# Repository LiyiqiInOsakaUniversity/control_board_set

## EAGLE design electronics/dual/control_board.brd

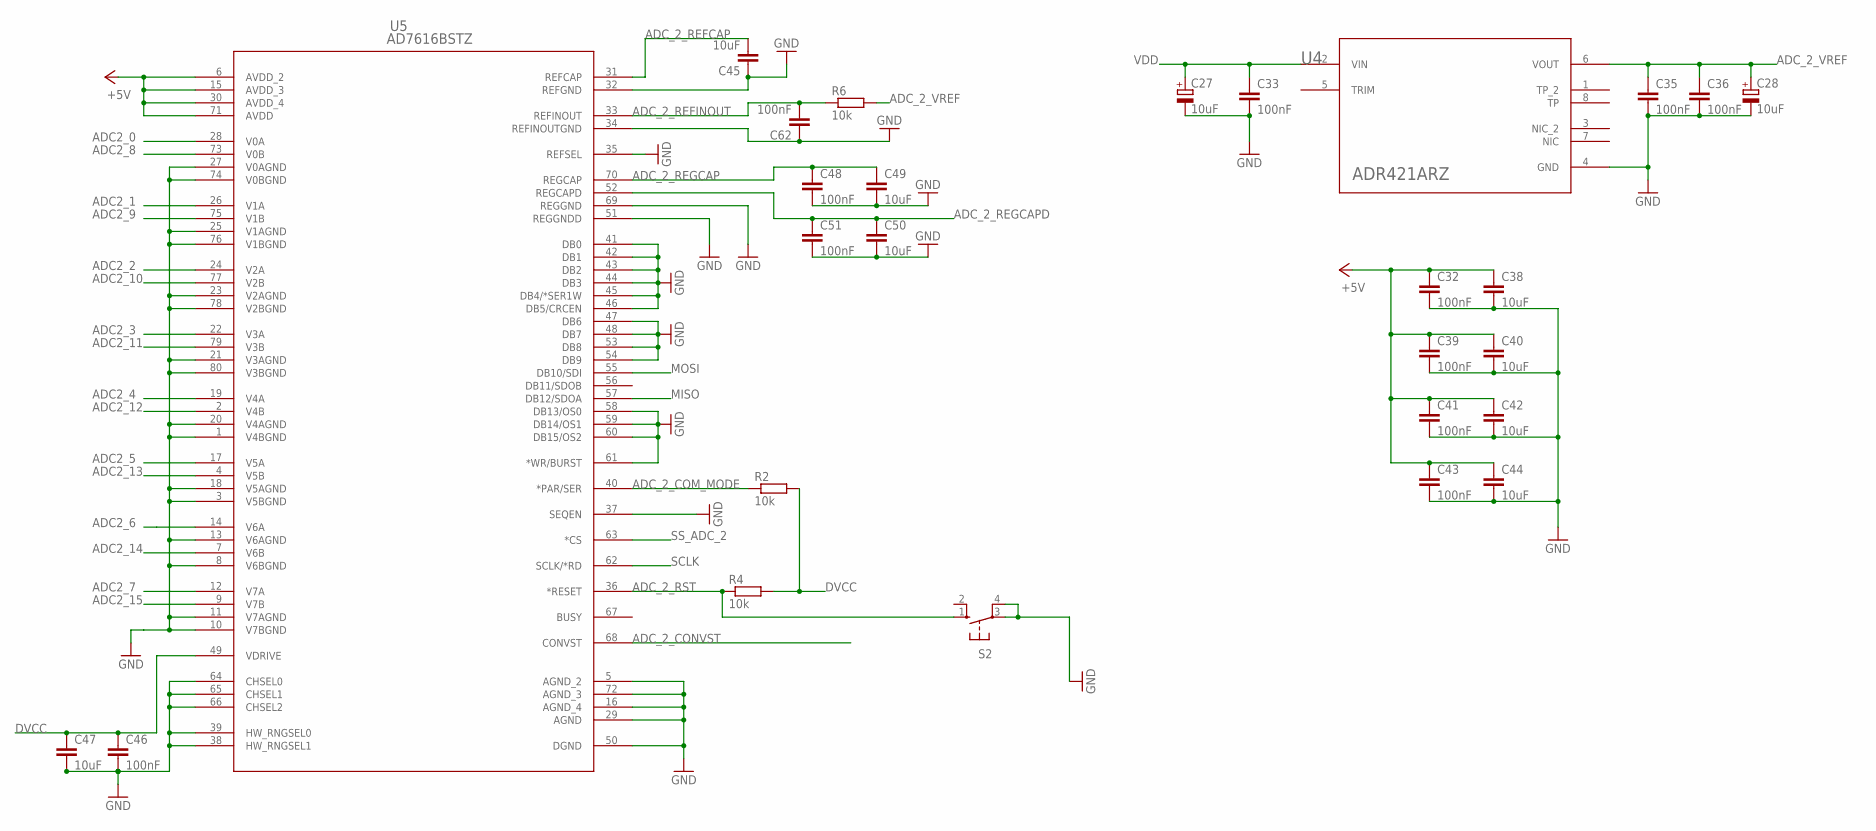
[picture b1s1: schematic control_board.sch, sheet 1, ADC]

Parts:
C27, C28: 10uF; SMC_A
C32, C33, C35, C36, C39, C41, C43, C46, C48, C51, C62: 100nF; C0603
C38, C40, C42, C44, C45, C47, C49, C50: 10uF; C0603
R2, R4, R6: 10k; R0603
S2: 10-XX; B3F-10XX
U4: ADR421ARZ; R_8
U5: AD7616BSTZ; ST_80_2

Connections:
+5V: C32.1, C38.1, C39.1, C40.1, C41.1, C42.1, C43.1, C44.1, U5.6 (AVDD_2), U5.15 (AVDD_3), U5.30 (AVDD_4), U5.71 (AVDD); also elsewhere on the board
ADC2_0: U5.28 (V0A); also elsewhere on the board
ADC2_1: U5.26 (V1A); also elsewhere on the board
ADC2_2: U5.24 (V2A); also elsewhere on the board
ADC2_3: U5.22 (V3A); also elsewhere on the board
ADC2_4: U5.19 (V4A); also elsewhere on the board
ADC2_5: U5.17 (V5A); also elsewhere on the board
ADC2_6: U5.14 (V6A); also elsewhere on the board
ADC2_7: U5.12 (V7A); also elsewhere on the board
ADC2_8: U5.73 (V0B); also elsewhere on the board
ADC2_9: U5.75 (V1B); also elsewhere on the board
ADC2_10: U5.77 (V2B); also elsewhere on the board
ADC2_11: U5.79 (V3B); also elsewhere on the board
ADC2_12: U5.2 (V4B); also elsewhere on the board
ADC2_13: U5.4 (V5B); also elsewhere on the board
ADC2_14: U5.7 (V6B); also elsewhere on the board
ADC2_15: U5.9 (V7B); also elsewhere on the board
ADC_2_COM_MODE: R2.1, U5.40 (*PAR/SER)
ADC_2_CONVST: U5.68 (CONVST); also elsewhere on the board
ADC_2_REFCAP: C45.2, U5.31 (REFCAP)
ADC_2_REFINOUT: C62.2, R6.1, U5.33 (REFINOUT)
ADC_2_REGCAP: C48.1, C49.1, U5.70 (REGCAP)
ADC_2_REGCAPD: C50.1, C51.1, U5.52 (REGCAPD)
ADC_2_RST: R4.1, S2.1 (S), U5.36 (*RESET)
ADC_2_VREF: C28.+, C35.1, C36.1, R6.2, U4.6 (VOUT)
DVCC: C46.1, C47.1, R2.2, R4.2, U5.49 (VDRIVE); also elsewhere on the board
GND: C27.-, C28.-, C32.2, C33.2, C35.2, C36.2, C38.2, C39.2, C40.2, C41.2, C42.2, C43.2, C44.2, C45.1, C46.2, C47.2, C48.2, C49.2, C50.2, C51.2, C62.1, S2.3, S2.4 (P1), U4.4 (GND), U5.1 (V4BGND), U5.3 (V5BGND), U5.5 (AGND_2), U5.8 (V6BGND), U5.10 (V7BGND), U5.11 (V7AGND), U5.13 (V6AGND), U5.16 (AGND_4), U5.18 (V5AGND), U5.20 (V4AGND), U5.21 (V3AGND), U5.23 (V2AGND), U5.25 (V1AGND), U5.27 (V0AGND), U5.29 (AGND), U5.32 (REFGND), U5.34 (REFINOUTGND), U5.35 (REFSEL), U5.37 (SEQEN), U5.38 (HW_RNGSEL1), U5.39 (HW_RNGSEL0), U5.41 (DB0), U5.42 (DB1), U5.43 (DB2), U5.44 (DB3), U5.45 (DB4/*SER1W), U5.46 (DB5/CRCEN), U5.47 (DB6), U5.48 (DB7), U5.50 (DGND), U5.51 (REGGNDD), U5.53 (DB8), U5.54 (DB9), U5.58 (DB13/OS0), U5.59 (DB14/OS1), U5.60 (DB15/OS2), U5.61 (*WR/BURST), U5.64 (CHSEL0), U5.65 (CHSEL1), U5.66 (CHSEL2), U5.69 (REGGND), U5.72 (AGND_3), U5.74 (V0BGND), U5.76 (V1BGND), U5.78 (V2BGND), U5.80 (V3BGND); also elsewhere on the board
MISO: U5.57 (DB12/SDOA); also elsewhere on the board
MOSI: U5.55 (DB10/SDI); also elsewhere on the board
SCLK: U5.62 (SCLK/*RD); also elsewhere on the board
SS_ADC_2: U5.63 (*CS); also elsewhere on the board
VDD: C27.+, C33.1, U4.2 (VIN); also elsewhere on the board

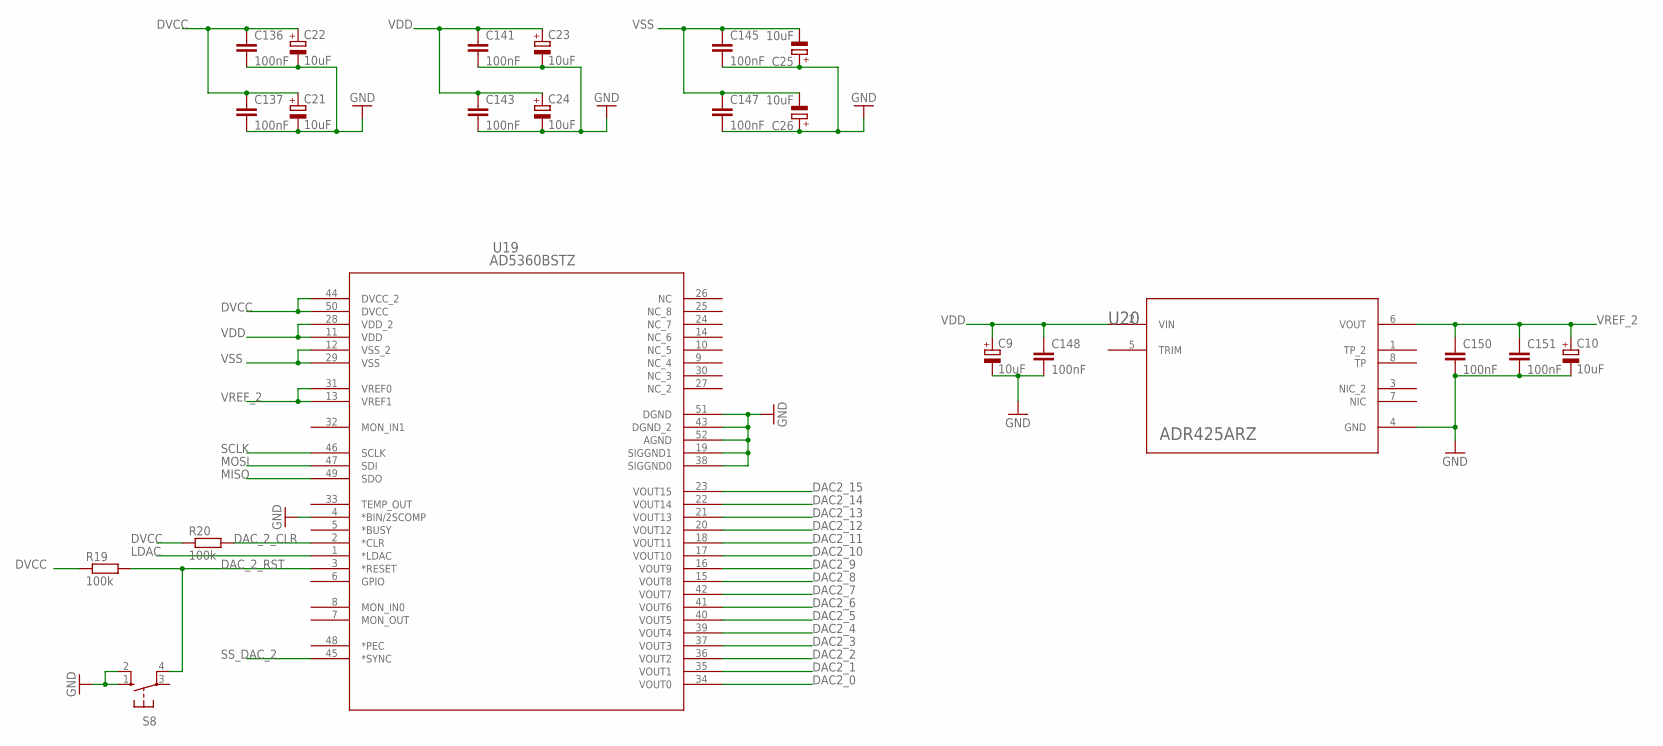
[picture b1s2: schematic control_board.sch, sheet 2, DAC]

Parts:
C9, C10, C21, C22, C23, C24, C25, C26: 10uF; SMC_A
C136, C137, C141, C143, C145, C147, C148, C150, C151: 100nF; C0603
R19, R20: 100k; R0603
S8: 10-XX; B3F-10XX
U19: AD5360BSTZ; ST_52
U20: ADR425ARZ; R_8

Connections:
DAC2_0: U19.34 (VOUT0); also elsewhere on the board
DAC2_1: U19.35 (VOUT1); also elsewhere on the board
DAC2_2: U19.36 (VOUT2); also elsewhere on the board
DAC2_3: U19.37 (VOUT3); also elsewhere on the board
DAC2_4: U19.39 (VOUT4); also elsewhere on the board
DAC2_5: U19.40 (VOUT5); also elsewhere on the board
DAC2_6: U19.41 (VOUT6); also elsewhere on the board
DAC2_7: U19.42 (VOUT7); also elsewhere on the board
DAC2_8: U19.15 (VOUT8); also elsewhere on the board
DAC2_9: U19.16 (VOUT9); also elsewhere on the board
DAC2_10: U19.17 (VOUT10); also elsewhere on the board
DAC2_11: U19.18 (VOUT11); also elsewhere on the board
DAC2_12: U19.20 (VOUT12); also elsewhere on the board
DAC2_13: U19.21 (VOUT13); also elsewhere on the board
DAC2_14: U19.22 (VOUT14); also elsewhere on the board
DAC2_15: U19.23 (VOUT15); also elsewhere on the board
DAC_2_CLR: R20.2, U19.2 (*CLR)
DAC_2_RST: R19.2, S8.4 (P1), U19.3 (*RESET)
DVCC: C21.+, C22.+, C136.1, C137.1, R19.1, R20.1, U19.44 (DVCC_2), U19.50 (DVCC); also elsewhere on the board
GND: C9.-, C10.-, C21.-, C22.-, C23.-, C24.-, C25.+, C26.+, C136.2, C137.2, C141.2, C143.2, C145.2, C147.2, C148.2, C150.2, C151.2, S8.1 (S), S8.2 (S1), U19.4 (*BIN/2SCOMP), U19.19 (SIGGND1), U19.38 (SIGGND0), U19.43 (DGND_2), U19.51 (DGND), U19.52 (AGND), U20.4 (GND); also elsewhere on the board
LDAC: U19.1 (*LDAC); also elsewhere on the board
MISO: U19.49 (SDO); also elsewhere on the board
MOSI: U19.47 (SDI); also elsewhere on the board
SCLK: U19.46 (SCLK); also elsewhere on the board
SS_DAC_2: U19.45 (*SYNC); also elsewhere on the board
VDD: C9.+, C23.+, C24.+, C141.1, C143.1, C148.1, U19.11 (VDD), U19.28 (VDD_2), U20.2 (VIN); also elsewhere on the board
VREF_2: C10.+, C150.1, C151.1, U19.13 (VREF1), U19.31 (VREF0), U20.6 (VOUT)
VSS: C25.-, C26.-, C145.1, C147.1, U19.12 (VSS_2), U19.29 (VSS); also elsewhere on the board

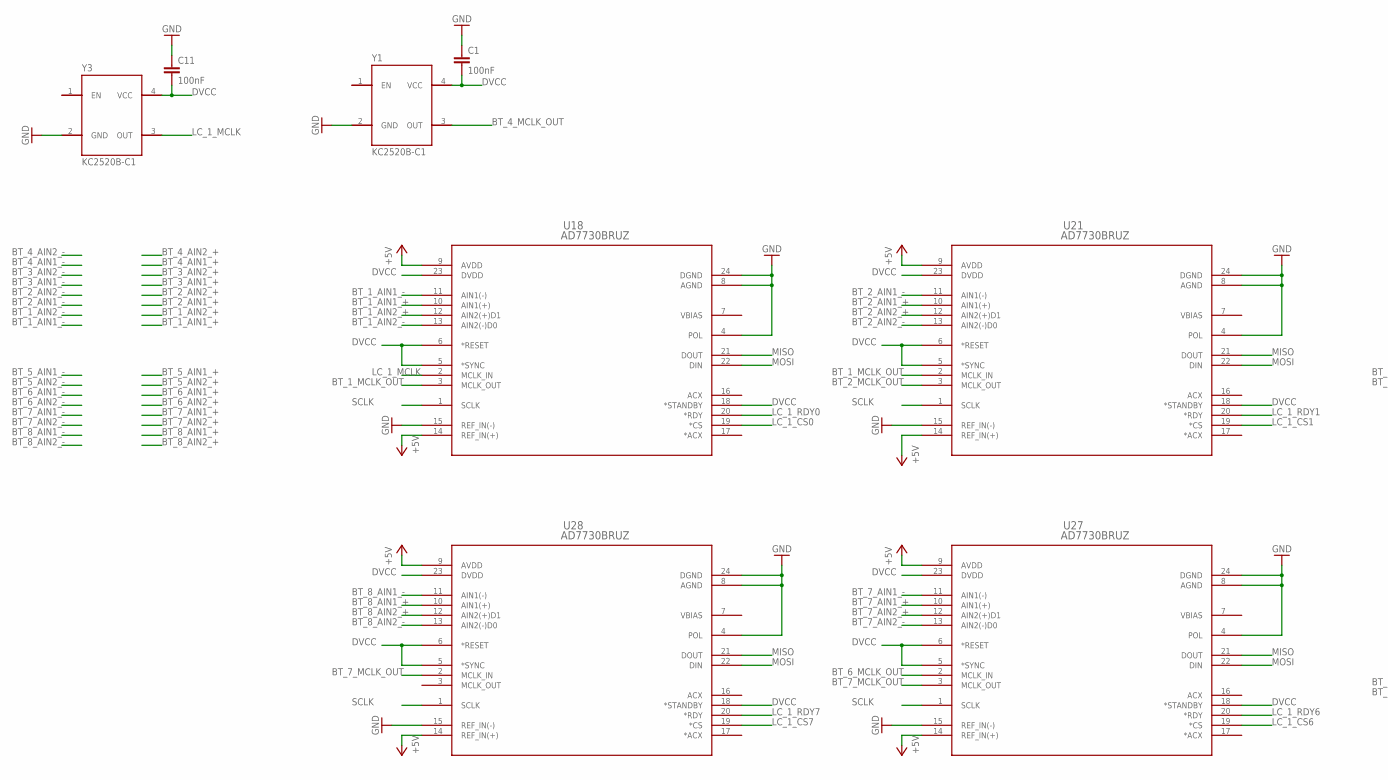
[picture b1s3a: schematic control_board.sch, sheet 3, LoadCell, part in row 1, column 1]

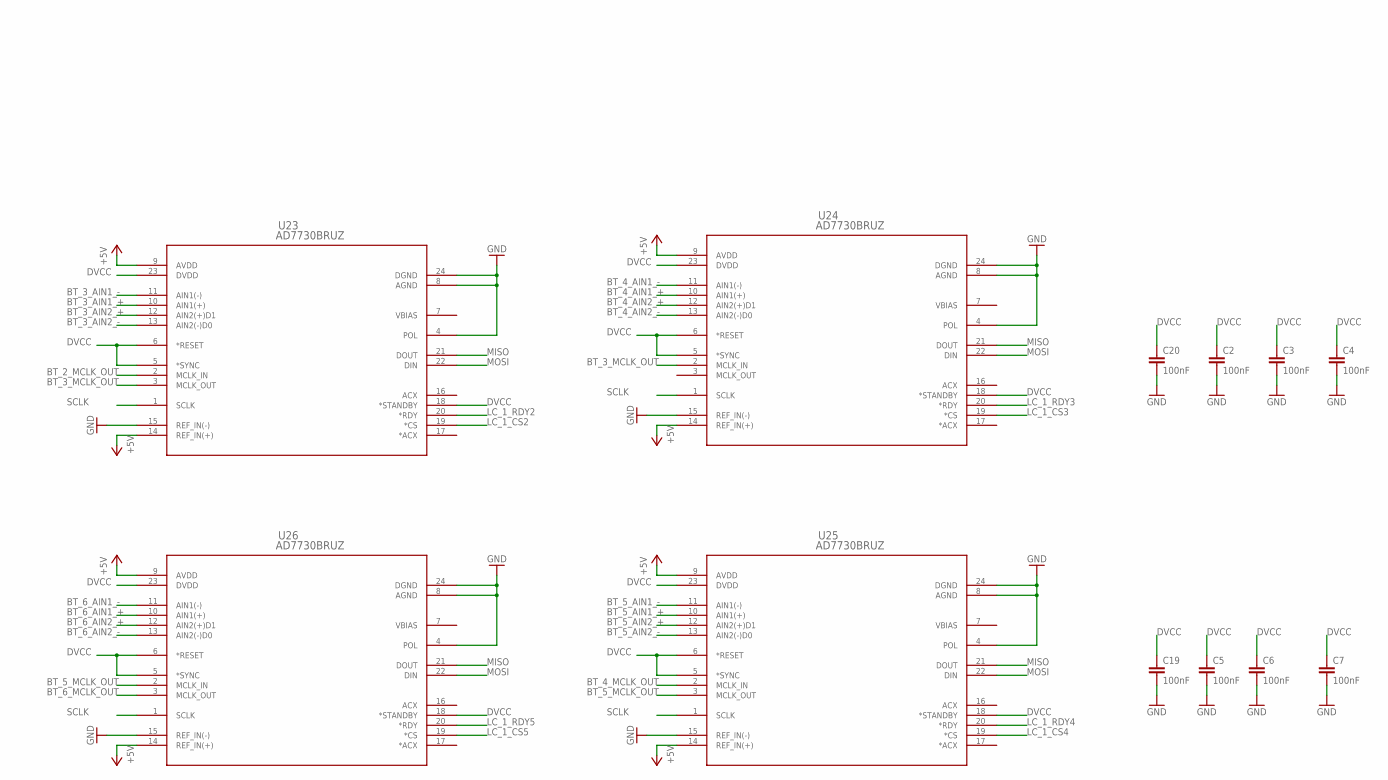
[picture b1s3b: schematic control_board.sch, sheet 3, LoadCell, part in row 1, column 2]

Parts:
C1, C2, C3, C4, C5, C6, C7, C11, C19, C20: 100nF; C0603
U18, U21, U23, U24, U25, U26, U27, U28: AD7730BRUZ; RU_24
Y1, Y3: KC2520B-C1

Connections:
+5V: U18.9 (AVDD), U18.14 (REF_IN(+)), U21.9 (AVDD), U21.14 (REF_IN(+)), U23.9 (AVDD), U23.14 (REF_IN(+)), U24.9 (AVDD), U24.14 (REF_IN(+)), U25.9 (AVDD), U25.14 (REF_IN(+)), U26.9 (AVDD), U26.14 (REF_IN(+)), U27.9 (AVDD), U27.14 (REF_IN(+)), U28.9 (AVDD), U28.14 (REF_IN(+)); also elsewhere on the board
BT_1_AIN1_+: U18.10 (AIN1(+)); also elsewhere on the board
BT_1_AIN1_-: U18.11 (AIN1(-)); also elsewhere on the board
BT_1_AIN2_+: U18.12 (AIN2(+)D1); also elsewhere on the board
BT_1_AIN2_-: U18.13 (AIN2(-)D0); also elsewhere on the board
BT_1_MCLK_OUT: U18.3 (MCLK_OUT), U21.2 (MCLK_IN)
BT_2_AIN1_+: U21.10 (AIN1(+)); also elsewhere on the board
BT_2_AIN1_-: U21.11 (AIN1(-)); also elsewhere on the board
BT_2_AIN2_+: U21.12 (AIN2(+)D1); also elsewhere on the board
BT_2_AIN2_-: U21.13 (AIN2(-)D0); also elsewhere on the board
BT_2_MCLK_OUT: U21.3 (MCLK_OUT), U23.2 (MCLK_IN)
BT_3_AIN1_+: U23.10 (AIN1(+)); also elsewhere on the board
BT_3_AIN1_-: U23.11 (AIN1(-)); also elsewhere on the board
BT_3_AIN2_+: U23.12 (AIN2(+)D1); also elsewhere on the board
BT_3_AIN2_-: U23.13 (AIN2(-)D0); also elsewhere on the board
BT_3_MCLK_OUT: U23.3 (MCLK_OUT), U24.2 (MCLK_IN)
BT_4_AIN1_+: U24.10 (AIN1(+)); also elsewhere on the board
BT_4_AIN1_-: U24.11 (AIN1(-)); also elsewhere on the board
BT_4_AIN2_+: U24.12 (AIN2(+)D1); also elsewhere on the board
BT_4_AIN2_-: U24.13 (AIN2(-)D0); also elsewhere on the board
BT_4_MCLK_OUT: U25.2 (MCLK_IN), Y1.3 (OUT)
BT_5_AIN1_+: U25.10 (AIN1(+)); also elsewhere on the board
BT_5_AIN1_-: U25.11 (AIN1(-)); also elsewhere on the board
BT_5_AIN2_+: U25.12 (AIN2(+)D1); also elsewhere on the board
BT_5_AIN2_-: U25.13 (AIN2(-)D0); also elsewhere on the board
BT_5_MCLK_OUT: U25.3 (MCLK_OUT), U26.2 (MCLK_IN)
BT_6_AIN1_+: U26.10 (AIN1(+)); also elsewhere on the board
BT_6_AIN1_-: U26.11 (AIN1(-)); also elsewhere on the board
BT_6_AIN2_+: U26.12 (AIN2(+)D1); also elsewhere on the board
BT_6_AIN2_-: U26.13 (AIN2(-)D0); also elsewhere on the board
BT_6_MCLK_OUT: U26.3 (MCLK_OUT), U27.2 (MCLK_IN)
BT_7_AIN1_+: U27.10 (AIN1(+)); also elsewhere on the board
BT_7_AIN1_-: U27.11 (AIN1(-)); also elsewhere on the board
BT_7_AIN2_+: U27.12 (AIN2(+)D1); also elsewhere on the board
BT_7_AIN2_-: U27.13 (AIN2(-)D0); also elsewhere on the board
BT_7_MCLK_OUT: U27.3 (MCLK_OUT), U28.2 (MCLK_IN)
BT_8_AIN1_+: U28.10 (AIN1(+)); also elsewhere on the board
BT_8_AIN1_-: U28.11 (AIN1(-)); also elsewhere on the board
BT_8_AIN2_+: U28.12 (AIN2(+)D1); also elsewhere on the board
BT_8_AIN2_-: U28.13 (AIN2(-)D0); also elsewhere on the board
DVCC: C1.2, C2.1, C3.1, C4.1, C5.1, C6.1, C7.1, C11.2, C19.1, C20.1, U18.5 (*SYNC), U18.6 (*RESET), U18.18 (*STANDBY), U18.23 (DVDD), U21.5 (*SYNC), U21.6 (*RESET), U21.18 (*STANDBY), U21.23 (DVDD), U23.5 (*SYNC), U23.6 (*RESET), U23.18 (*STANDBY), U23.23 (DVDD), U24.5 (*SYNC), U24.6 (*RESET), U24.18 (*STANDBY), U24.23 (DVDD), U25.5 (*SYNC), U25.6 (*RESET), U25.18 (*STANDBY), U25.23 (DVDD), U26.5 (*SYNC), U26.6 (*RESET), U26.18 (*STANDBY), U26.23 (DVDD), U27.5 (*SYNC), U27.6 (*RESET), U27.18 (*STANDBY), U27.23 (DVDD), U28.5 (*SYNC), U28.6 (*RESET), U28.18 (*STANDBY), U28.23 (DVDD), Y1.4 (VCC), Y3.4 (VCC); also elsewhere on the board
GND: C1.1, C2.2, C3.2, C4.2, C5.2, C6.2, C7.2, C11.1, C19.2, C20.2, U18.4 (POL), U18.8 (AGND), U18.15 (REF_IN(-)), U18.24 (DGND), U21.4 (POL), U21.8 (AGND), U21.15 (REF_IN(-)), U21.24 (DGND), U23.4 (POL), U23.8 (AGND), U23.15 (REF_IN(-)), U23.24 (DGND), U24.4 (POL), U24.8 (AGND), U24.15 (REF_IN(-)), U24.24 (DGND), U25.4 (POL), U25.8 (AGND), U25.15 (REF_IN(-)), U25.24 (DGND), U26.4 (POL), U26.8 (AGND), U26.15 (REF_IN(-)), U26.24 (DGND), U27.4 (POL), U27.8 (AGND), U27.15 (REF_IN(-)), U27.24 (DGND), U28.4 (POL), U28.8 (AGND), U28.15 (REF_IN(-)), U28.24 (DGND), Y1.2 (GND), Y3.2 (GND); also elsewhere on the board
LC_1_CS0: U18.19 (*CS); also elsewhere on the board
LC_1_CS1: U21.19 (*CS); also elsewhere on the board
LC_1_CS2: U23.19 (*CS); also elsewhere on the board
LC_1_CS3: U24.19 (*CS); also elsewhere on the board
LC_1_CS4: U25.19 (*CS); also elsewhere on the board
LC_1_CS5: U26.19 (*CS); also elsewhere on the board
LC_1_CS6: U27.19 (*CS); also elsewhere on the board
LC_1_CS7: U28.19 (*CS); also elsewhere on the board
LC_1_MCLK: U18.2 (MCLK_IN), Y3.3 (OUT)
LC_1_RDY0: U18.20 (*RDY); also elsewhere on the board
LC_1_RDY1: U21.20 (*RDY); also elsewhere on the board
LC_1_RDY2: U23.20 (*RDY); also elsewhere on the board
LC_1_RDY3: U24.20 (*RDY); also elsewhere on the board
LC_1_RDY4: U25.20 (*RDY); also elsewhere on the board
LC_1_RDY5: U26.20 (*RDY); also elsewhere on the board
LC_1_RDY6: U27.20 (*RDY); also elsewhere on the board
LC_1_RDY7: U28.20 (*RDY); also elsewhere on the board
MISO: U18.21 (DOUT), U21.21 (DOUT), U23.21 (DOUT), U24.21 (DOUT), U25.21 (DOUT), U26.21 (DOUT), U27.21 (DOUT), U28.21 (DOUT); also elsewhere on the board
MOSI: U18.22 (DIN), U21.22 (DIN), U23.22 (DIN), U24.22 (DIN), U25.22 (DIN), U26.22 (DIN), U27.22 (DIN), U28.22 (DIN); also elsewhere on the board
SCLK: U18.1 (SCLK), U21.1 (SCLK), U23.1 (SCLK), U24.1 (SCLK), U25.1 (SCLK), U26.1 (SCLK), U27.1 (SCLK), U28.1 (SCLK); also elsewhere on the board

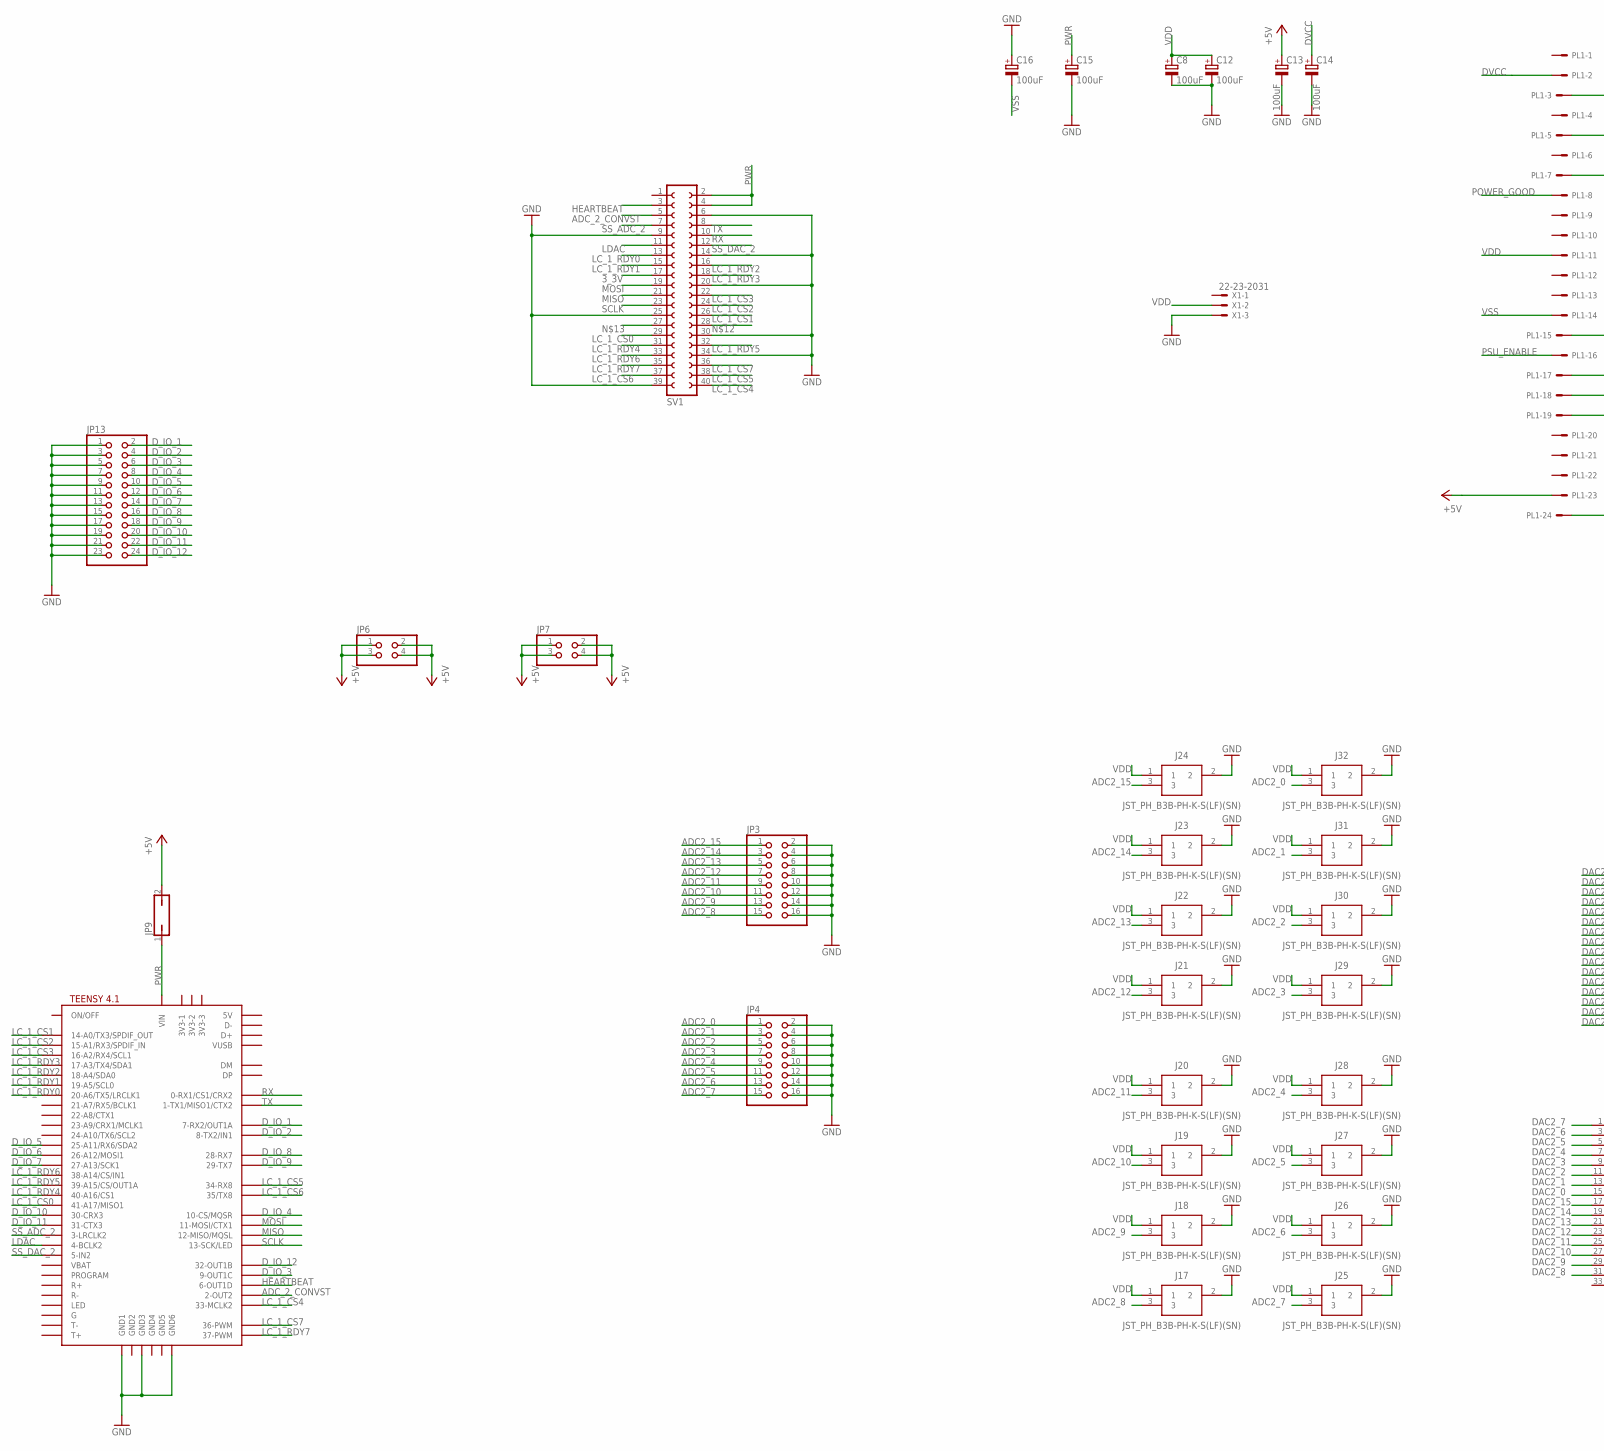
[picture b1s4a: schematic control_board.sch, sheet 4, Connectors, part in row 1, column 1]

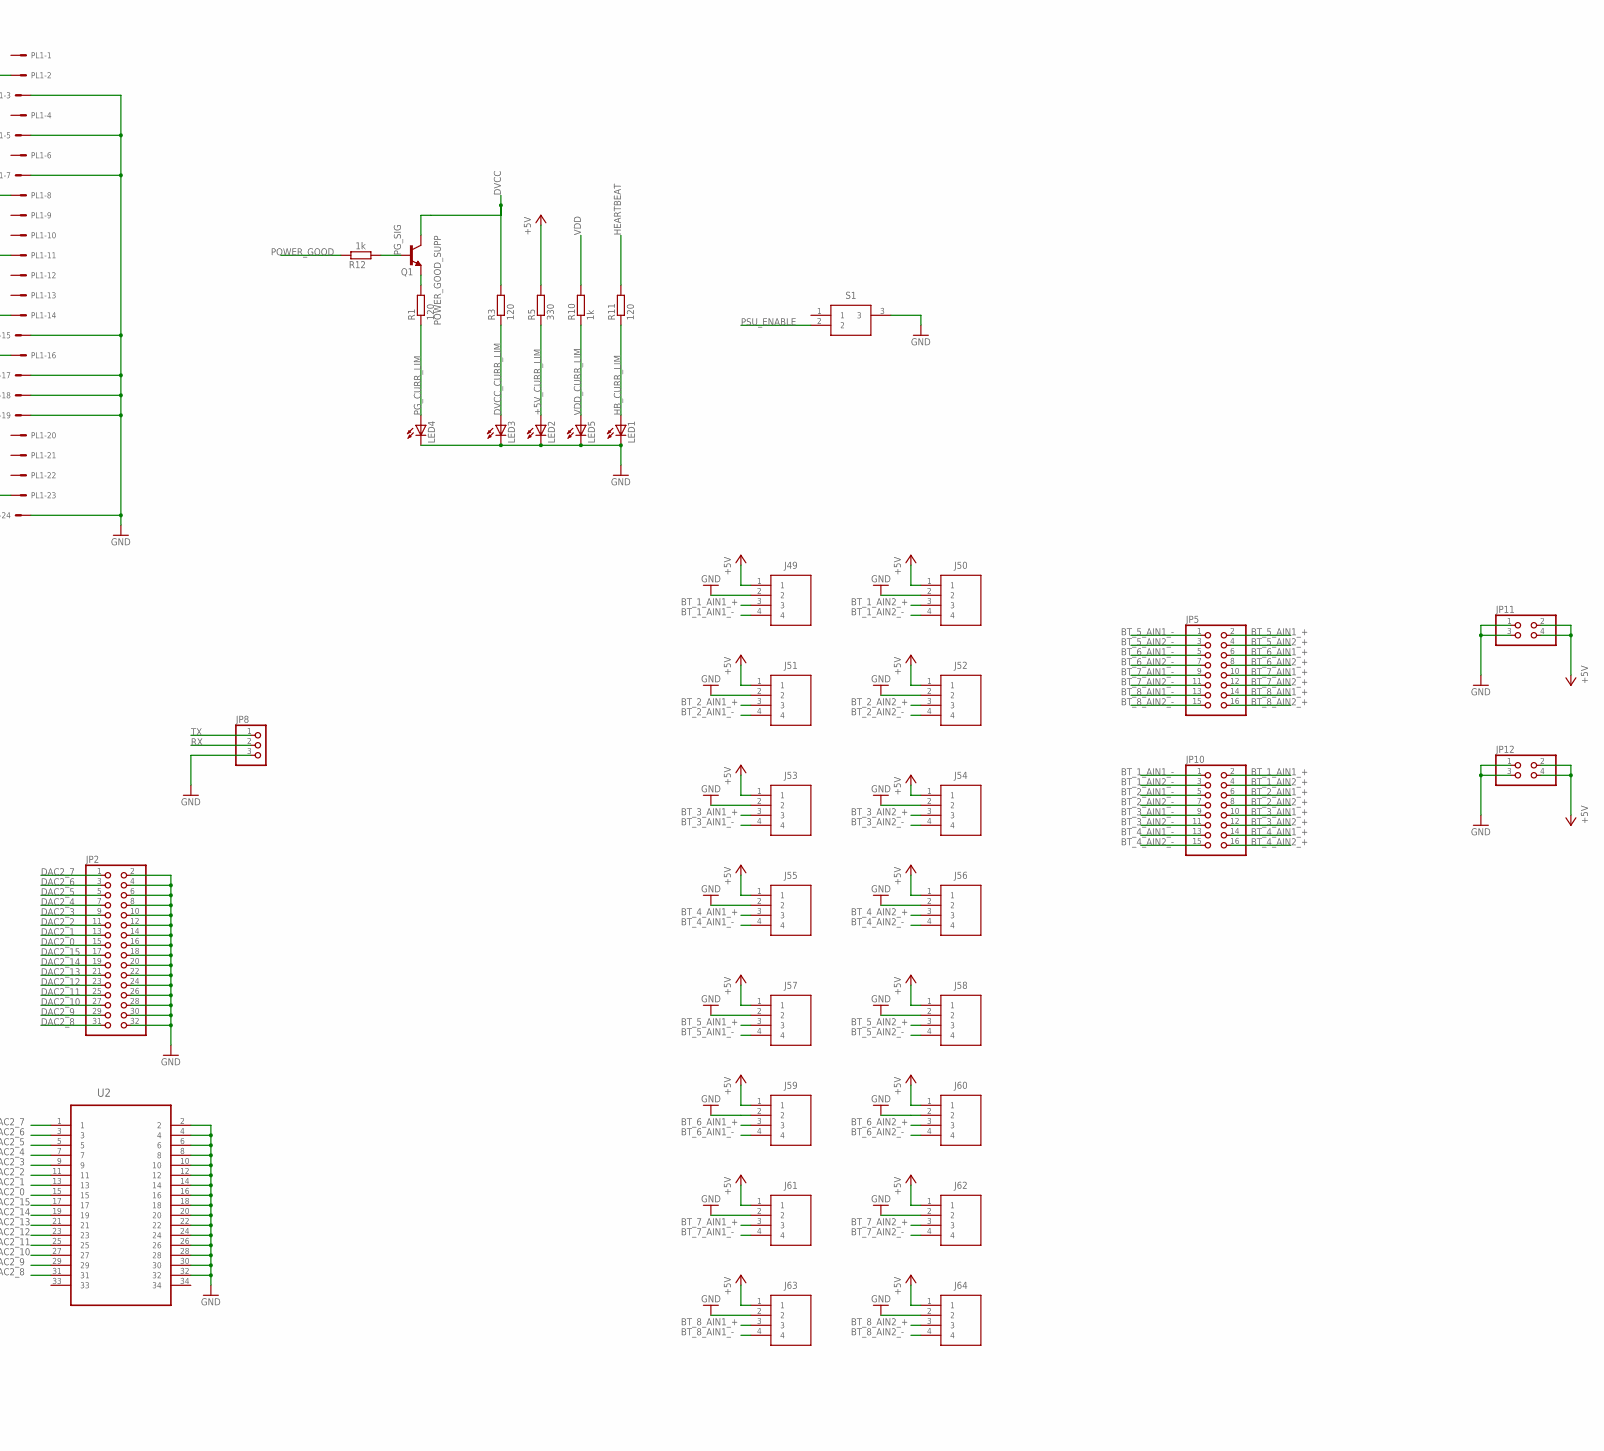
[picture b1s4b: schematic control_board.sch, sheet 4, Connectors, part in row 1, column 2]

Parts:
C8, C12, C13, C14, C15, C16: 100uF; E3,5-8
J17, J18, J19, J20, J21, J22, J23, J24, J25, J26, J27, J28, J29, J30, J31, J32: JST_PH_B3B-PH-K-S(LF)(SN); JST_PH_SHDR3W50P0X200_1X3_790X450X600
J49, J50, J51, J52, J53, J54, J55, J56, J57, J58, J59, J60, J61, J62, J63, J64: B4B-PH-K-S(LF)(SN); SHDR4W50P0X200_1X4_990X450X600
JP2: PINHD-2X16/90; 2X16/90
JP3, JP4: PINHD-2X8/90; 2X08/90
JP5, JP10: PINHD-2X8; 2X08
JP6, JP7: PINHD-2X2/90; 2X02/90
JP8: PINHD-1X3; 1X03
JP9: JP1Q; JP1
JP11, JP12: PINHD-2X2; 2X02
JP13: PINHD-2X12_2.54-SMD; 2X12SMD
LED1, LED2, LED3, LED4, LED5: LEDCHIP-LED0603; CHIP-LED0603
PL1: 555X-24V; 5566-24
Q1: BCF29SMD; SOT23-BEC
R1, R3, R11: 120; R0805
R5: 330; R0805
R10, R12: 1k; R0805
S1: 1MS1T1B1M2QES-5
SV1: FE20-2
U2: AMP-5103309-7-34PIN_5103309-7; AMP-5103309-7-34PIN_TYCO_5103309-7
U$1: TEENSY41
X1: 22-23-2031

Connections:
3_3V: SV1.17
+5V: C13.+, J49.1, J50.1, J51.1, J52.1, J53.1, J54.1, J55.1, J56.1, J57.1, J58.1, J59.1, J60.1, J61.1, J62.1, J63.1, J64.1, JP6.1, JP6.2, JP6.3, JP6.4, JP7.1, JP7.2, JP7.3, JP7.4, JP9.2, JP11.2, JP11.4, JP12.2, JP12.4, PL1.23, R5.2; also elsewhere on the board
+5V_CURR_LIM: LED2.A, R5.1
ADC2_0: J32.3, JP4.1; also elsewhere on the board
ADC2_1: J31.3, JP4.3; also elsewhere on the board
ADC2_2: J30.3, JP4.5; also elsewhere on the board
ADC2_3: J29.3, JP4.7; also elsewhere on the board
ADC2_4: J28.3, JP4.9; also elsewhere on the board
ADC2_5: J27.3, JP4.11; also elsewhere on the board
ADC2_6: J26.3, JP4.13; also elsewhere on the board
ADC2_7: J25.3, JP4.15; also elsewhere on the board
ADC2_8: J17.3, JP3.15; also elsewhere on the board
ADC2_9: J18.3, JP3.13; also elsewhere on the board
ADC2_10: J19.3, JP3.11; also elsewhere on the board
ADC2_11: J20.3, JP3.9; also elsewhere on the board
ADC2_12: J21.3, JP3.7; also elsewhere on the board
ADC2_13: J22.3, JP3.5; also elsewhere on the board
ADC2_14: J23.3, JP3.3; also elsewhere on the board
ADC2_15: J24.3, JP3.1; also elsewhere on the board
ADC_2_CONVST: SV1.5, U$1.2-OUT2; also elsewhere on the board
BT_1_AIN1_+: J49.3, JP10.2; also elsewhere on the board
BT_1_AIN1_-: J49.4, JP10.1; also elsewhere on the board
BT_1_AIN2_+: J50.3, JP10.4; also elsewhere on the board
BT_1_AIN2_-: J50.4, JP10.3; also elsewhere on the board
BT_2_AIN1_+: J51.3, JP10.6; also elsewhere on the board
BT_2_AIN1_-: J51.4, JP10.5; also elsewhere on the board
BT_2_AIN2_+: J52.3, JP10.8; also elsewhere on the board
BT_2_AIN2_-: J52.4, JP10.7; also elsewhere on the board
BT_3_AIN1_+: J53.3, JP10.10; also elsewhere on the board
BT_3_AIN1_-: J53.4, JP10.9; also elsewhere on the board
BT_3_AIN2_+: J54.3, JP10.12; also elsewhere on the board
BT_3_AIN2_-: J54.4, JP10.11; also elsewhere on the board
BT_4_AIN1_+: J55.3, JP10.14; also elsewhere on the board
BT_4_AIN1_-: J55.4, JP10.13; also elsewhere on the board
BT_4_AIN2_+: J56.3, JP10.16; also elsewhere on the board
BT_4_AIN2_-: J56.4, JP10.15; also elsewhere on the board
BT_5_AIN1_+: J57.3, JP5.2; also elsewhere on the board
BT_5_AIN1_-: J57.4, JP5.1; also elsewhere on the board
BT_5_AIN2_+: J58.3, JP5.4; also elsewhere on the board
BT_5_AIN2_-: J58.4, JP5.3; also elsewhere on the board
BT_6_AIN1_+: J59.3, JP5.6; also elsewhere on the board
BT_6_AIN1_-: J59.4, JP5.5; also elsewhere on the board
BT_6_AIN2_+: J60.3, JP5.8; also elsewhere on the board
BT_6_AIN2_-: J60.4, JP5.7; also elsewhere on the board
BT_7_AIN1_+: J61.3, JP5.10; also elsewhere on the board
BT_7_AIN1_-: J61.4, JP5.9; also elsewhere on the board
BT_7_AIN2_+: J62.3, JP5.12; also elsewhere on the board
BT_7_AIN2_-: J62.4, JP5.11; also elsewhere on the board
BT_8_AIN1_+: J63.3, JP5.14; also elsewhere on the board
BT_8_AIN1_-: J63.4, JP5.13; also elsewhere on the board
BT_8_AIN2_+: J64.3, JP5.16; also elsewhere on the board
BT_8_AIN2_-: J64.4, JP5.15; also elsewhere on the board
DAC2_0: JP2.15, U2.15; also elsewhere on the board
DAC2_1: JP2.13, U2.13; also elsewhere on the board
DAC2_2: JP2.11, U2.11; also elsewhere on the board
DAC2_3: JP2.9, U2.9; also elsewhere on the board
DAC2_4: JP2.7, U2.7; also elsewhere on the board
DAC2_5: JP2.5, U2.5; also elsewhere on the board
DAC2_6: JP2.3, U2.3; also elsewhere on the board
DAC2_7: JP2.1, U2.1; also elsewhere on the board
DAC2_8: JP2.31, U2.31; also elsewhere on the board
DAC2_9: JP2.29, U2.29; also elsewhere on the board
DAC2_10: JP2.27, U2.27; also elsewhere on the board
DAC2_11: JP2.25, U2.25; also elsewhere on the board
DAC2_12: JP2.23, U2.23; also elsewhere on the board
DAC2_13: JP2.21, U2.21; also elsewhere on the board
DAC2_14: JP2.19, U2.19; also elsewhere on the board
DAC2_15: JP2.17, U2.17; also elsewhere on the board
DVCC: C14.+, PL1.2, Q1.C, R3.2; also elsewhere on the board
DVCC_CURR_LIM: LED3.A, R3.1
D_IO_1: JP13.2, U$1.7-RX2/OUT1A
D_IO_2: JP13.4, U$1.8-TX2/IN2 (8-TX2/IN1)
D_IO_3: JP13.6, U$1.9-OUT1C
D_IO_4: JP13.8, U$1.10-CS\MQSR (10-CS/MQSR)
D_IO_5: JP13.10, U$1.25-A11/RX6/SDA2
D_IO_6: JP13.12, U$1.26-A12/MOSI1
D_IO_7: JP13.14, U$1.27-A13/SCK1
D_IO_8: JP13.16, U$1.28-RX7
D_IO_9: JP13.18, U$1.29-TX7
D_IO_10: JP13.20, U$1.30-CRX3
D_IO_11: JP13.22, U$1.31-CTX3
D_IO_12: JP13.24, U$1.32-OUT1B
GND: C8.-, C12.-, C13.-, C14.-, C15.-, C16.+, J17.2, J18.2, J19.2, J20.2, J21.2, J22.2, J23.2, J24.2, J25.2, J26.2, J27.2, J28.2, J29.2, J30.2, J31.2, J32.2, J49.2, J50.2, J51.2, J52.2, J53.2, J54.2, J55.2, J56.2, J57.2, J58.2, J59.2, J60.2, J61.2, J62.2, J63.2, J64.2, JP2.2, JP2.4, JP2.6, JP2.8, JP2.10, JP2.12, JP2.14, JP2.16, JP2.18, JP2.20, JP2.22, JP2.24, JP2.26, JP2.28, JP2.30, JP2.32, JP3.2, JP3.4, JP3.6, JP3.8, JP3.10, JP3.12, JP3.14, JP3.16, JP4.2, JP4.4, JP4.6, JP4.8, JP4.10, JP4.12, JP4.14, JP4.16, JP8.3, JP11.1, JP11.3, JP12.1, JP12.3, JP13.1, JP13.3, JP13.5, JP13.7, JP13.9, JP13.11, JP13.13, JP13.15, JP13.17, JP13.19, JP13.21, JP13.23, LED1.C, LED2.C, LED3.C, LED4.C, LED5.C, PL1.3, PL1.5, PL1.7, PL1.15, PL1.17, PL1.18, PL1.19, PL1.24, S1.3, SV1.6, SV1.9, SV1.14, SV1.20, SV1.25, SV1.30, SV1.34, SV1.39, U2.2, U2.4, U2.6, U2.8, U2.10, U2.12, U2.14, U2.16, U2.18, U2.20, U2.22, U2.24, U2.26, U2.28, U2.30, U2.32, U$1.GND1, U$1.GND3, U$1.GND6, X1.3; also elsewhere on the board
HB_CURR_LIM: LED1.A, R11.1
HEARTBEAT: R11.2, SV1.3, U$1.6-OUT1D
LC_1_CS0: SV1.29, U$1.41-A17/MISO1; also elsewhere on the board
LC_1_CS1: SV1.26, U$1.14-A0/TX3/SPDIF_OUT; also elsewhere on the board
LC_1_CS2: SV1.24, U$1.15-A1/RX3/SPDIF_IN; also elsewhere on the board
LC_1_CS3: SV1.22, U$1.16-A2/RX4/SCL1; also elsewhere on the board
LC_1_CS4: SV1.40, U$1.33-MCLK2; also elsewhere on the board
LC_1_CS5: SV1.38, U$1.34-RX8; also elsewhere on the board
LC_1_CS6: SV1.37, U$1.35-TX8 (35/TX8); also elsewhere on the board
LC_1_CS7: SV1.36, U$1.36-PWM; also elsewhere on the board
LC_1_RDY0: SV1.13, U$1.20-A6/TX5/LRCLK1; also elsewhere on the board
LC_1_RDY1: SV1.15, U$1.19-A5/SCL0; also elsewhere on the board
LC_1_RDY2: SV1.16, U$1.18-A4/SDA0; also elsewhere on the board
LC_1_RDY3: SV1.18, U$1.17-A3/TX4/SDA1; also elsewhere on the board
LC_1_RDY4: SV1.31, U$1.40-A16/CS1; also elsewhere on the board
LC_1_RDY5: SV1.32, U$1.39-A15/CS/OUT1A; also elsewhere on the board
LC_1_RDY6: SV1.33, U$1.38-A14/CS/IN1; also elsewhere on the board
LC_1_RDY7: SV1.35, U$1.37-PWM; also elsewhere on the board
LDAC: SV1.11, U$1.4-BCLK2; also elsewhere on the board
MISO: SV1.21, U$1.12-MISO/MQSL; also elsewhere on the board
MOSI: SV1.19, U$1.11-MOSI/CTX1; also elsewhere on the board
PG_CURR_LIM: LED4.A, R1.1
PG_SIG: Q1.B, R12.1
POWER_GOOD: PL1.8, R12.2
POWER_GOOD_SUPP: Q1.E, R1.2
PSU_ENABLE: PL1.16, S1.2
PWR: C15.+, JP9.1, SV1.2, SV1.4, U$1.VIN
RX: JP8.2, SV1.10, U$1.0-RX1/CS1/CRX2
SCLK: SV1.23, U$1.13-SCK/LED; also elsewhere on the board
SS_ADC_2: SV1.7, U$1.3-LRCLK2; also elsewhere on the board
SS_DAC_2: SV1.12, U$1.5-IN2; also elsewhere on the board
TX: JP8.1, SV1.8, U$1.1-TX1/MISO1/CTX2
VDD: C8.+, C12.+, J17.1, J18.1, J19.1, J20.1, J21.1, J22.1, J23.1, J24.1, J25.1, J26.1, J27.1, J28.1, J29.1, J30.1, J31.1, J32.1, PL1.11, R10.2, X1.2; also elsewhere on the board
VDD_CURR_LIM: LED5.A, R10.1
VSS: C16.-, PL1.14; also elsewhere on the board
